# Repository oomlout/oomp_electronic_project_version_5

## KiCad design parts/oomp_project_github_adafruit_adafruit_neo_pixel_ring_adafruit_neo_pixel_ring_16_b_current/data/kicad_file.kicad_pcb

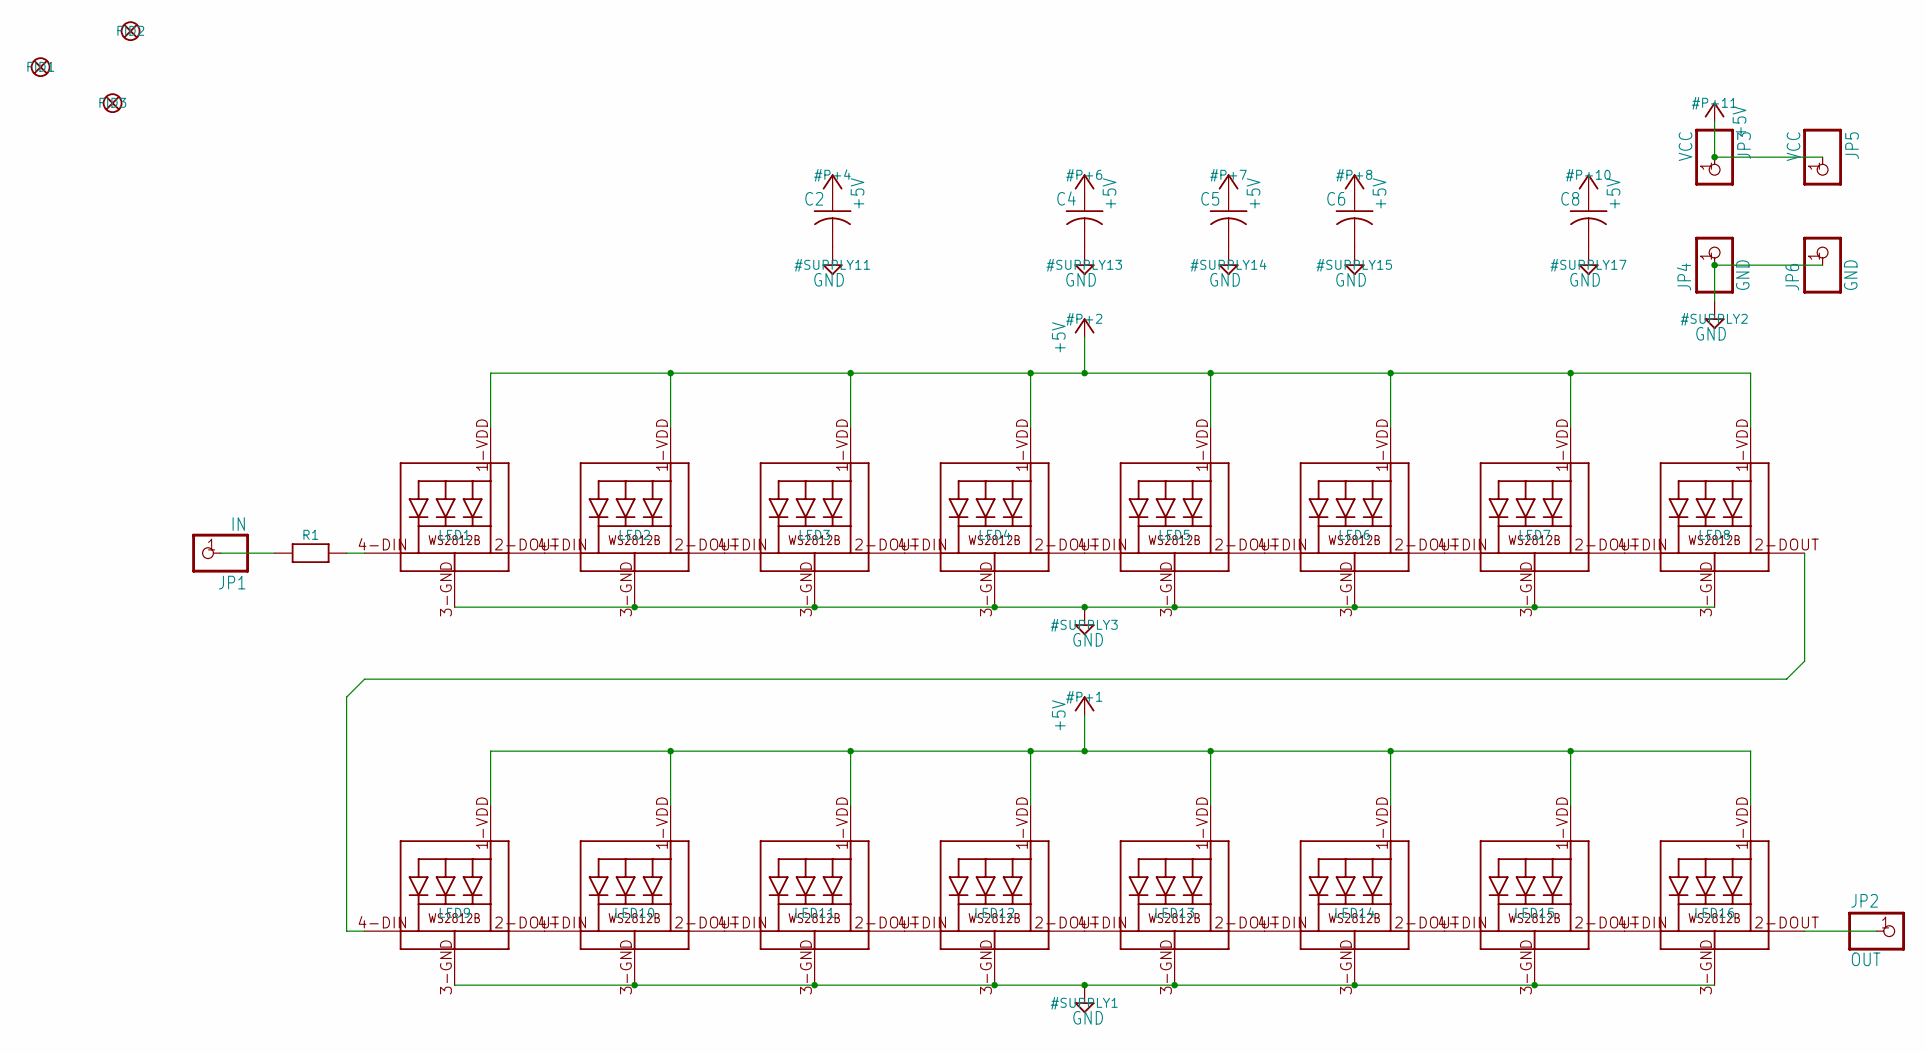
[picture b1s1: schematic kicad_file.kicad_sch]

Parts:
C2, C4, C5, C6, C8: C-USC0603K; C0603K
FID1, FID2, FID3: FIDUCIAL""; FIDUCIAL_1MM
JP1: IN; 1X01-CLEANBIG
JP2: OUT; 1X01-CLEANBIG
JP3, JP5: VCC; 1X01-CLEANBIG
JP4, JP6: GND; 1X01-CLEANBIG
LED1, LED2, LED3, LED4, LED5, LED6, LED7, LED8, LED9, LED10, LED11, LED12, LED13, LED14, LED15, LED16: WS2812B5050; WS2812B
R1: RESISTOR_0603_NOOUT; 0603-NO

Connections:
+5V: C2.1, C4.1, C5.1, C6.1, C8.1, JP3.1, JP5.1, LED1.1-VDD (VDD), LED2.1-VDD (VDD), LED3.1-VDD (VDD), LED4.1-VDD (VDD), LED5.1-VDD (VDD), LED6.1-VDD (VDD), LED7.1-VDD (VDD), LED8.1-VDD (VDD), LED9.1-VDD (VDD), LED10.1-VDD (VDD), LED11.1-VDD (VDD), LED12.1-VDD (VDD), LED13.1-VDD (VDD), LED14.1-VDD (VDD), LED15.1-VDD (VDD), LED16.1-VDD (VDD)
GND: C2.2, C4.2, C5.2, C6.2, C8.2, JP4.1, JP6.1, LED1.3-GND (GND), LED2.3-GND (GND), LED3.3-GND (GND), LED4.3-GND (GND), LED5.3-GND (GND), LED6.3-GND (GND), LED7.3-GND (GND), LED8.3-GND (GND), LED9.3-GND (GND), LED10.3-GND (GND), LED11.3-GND (GND), LED12.3-GND (GND), LED13.3-GND (GND), LED14.3-GND (GND), LED15.3-GND (GND), LED16.3-GND (GND)
IN: JP1.1, R1.1
unnamed: LED1.2-DOUT (DO), LED2.4-DIN (DI)
unnamed: LED2.2-DOUT (DO), LED3.4-DIN (DI)
unnamed: LED3.2-DOUT (DO), LED4.4-DIN (DI)
unnamed: LED4.2-DOUT (DO), LED5.4-DIN (DI)
unnamed: LED5.2-DOUT (DO), LED6.4-DIN (DI)
unnamed: LED6.2-DOUT (DO), LED7.4-DIN (DI)
unnamed: LED7.2-DOUT (DO), LED8.4-DIN (DI)
unnamed: LED1.4-DIN (DI), R1.2
unnamed: LED9.2-DOUT (DO), LED10.4-DIN (DI)
unnamed: LED10.2-DOUT (DO), LED11.4-DIN (DI)
unnamed: LED11.2-DOUT (DO), LED12.4-DIN (DI)
unnamed: LED12.2-DOUT (DO), LED13.4-DIN (DI)
unnamed: LED13.2-DOUT (DO), LED14.4-DIN (DI)
unnamed: LED14.2-DOUT (DO), LED15.4-DIN (DI)
unnamed: LED15.2-DOUT (DO), LED16.4-DIN (DI)
unnamed: LED8.2-DOUT (DO), LED9.4-DIN (DI)
OUT: JP2.1, LED16.2-DOUT (DO)

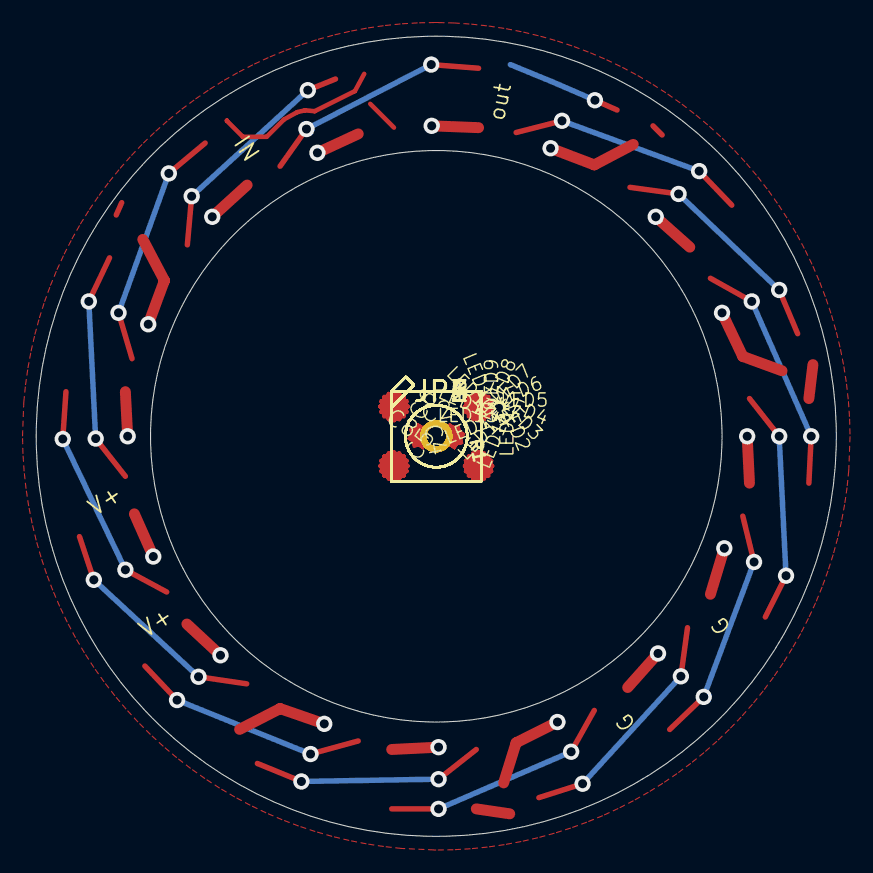
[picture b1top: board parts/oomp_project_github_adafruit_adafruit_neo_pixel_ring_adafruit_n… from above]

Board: 2 copper layers, 44.5 x 44.5 mm, 32 parts (1 on the bottom side), 20 nets.

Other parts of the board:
U$2: ADAFRUIT_5MM

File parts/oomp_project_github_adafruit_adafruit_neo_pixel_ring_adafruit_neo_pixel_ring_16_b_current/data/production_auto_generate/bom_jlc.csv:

Comment,Designator,Footprint,LCSC Part #
,R1,Adafruit NeoPixel Ring 16 B-import-fps:0603-NO,
,U$2,Adafruit NeoPixel Ring 16 B-import-fps:ADAFRUIT_5MM,
,"C2,C4,C5,C6,C8",Adafruit NeoPixel Ring 16 B-import-fps:C0603K,
GND,"JP4,JP6",Adafruit NeoPixel Ring 16 B-import-fps:1X01-CLEANBIG,C7501259
IN,JP1,Adafruit NeoPixel Ring 16 B-import-fps:1X01-CLEANBIG,C7501259
OUT,JP2,Adafruit NeoPixel Ring 16 B-import-fps:1X01-CLEANBIG,C7501259
VCC,"JP3,JP5",Adafruit NeoPixel Ring 16 B-import-fps:1X01-CLEANBIG,C7501259
WS2812B5050,"LED1,LED2,LED3,LED4,LED5,LED6,LED7,LED8,LED9,LED10,LED11,LED12,LED13,LED14,LED15,LED16",Adafruit NeoPixel Ring 16 B-import-fps:WS2812B-NARROW,

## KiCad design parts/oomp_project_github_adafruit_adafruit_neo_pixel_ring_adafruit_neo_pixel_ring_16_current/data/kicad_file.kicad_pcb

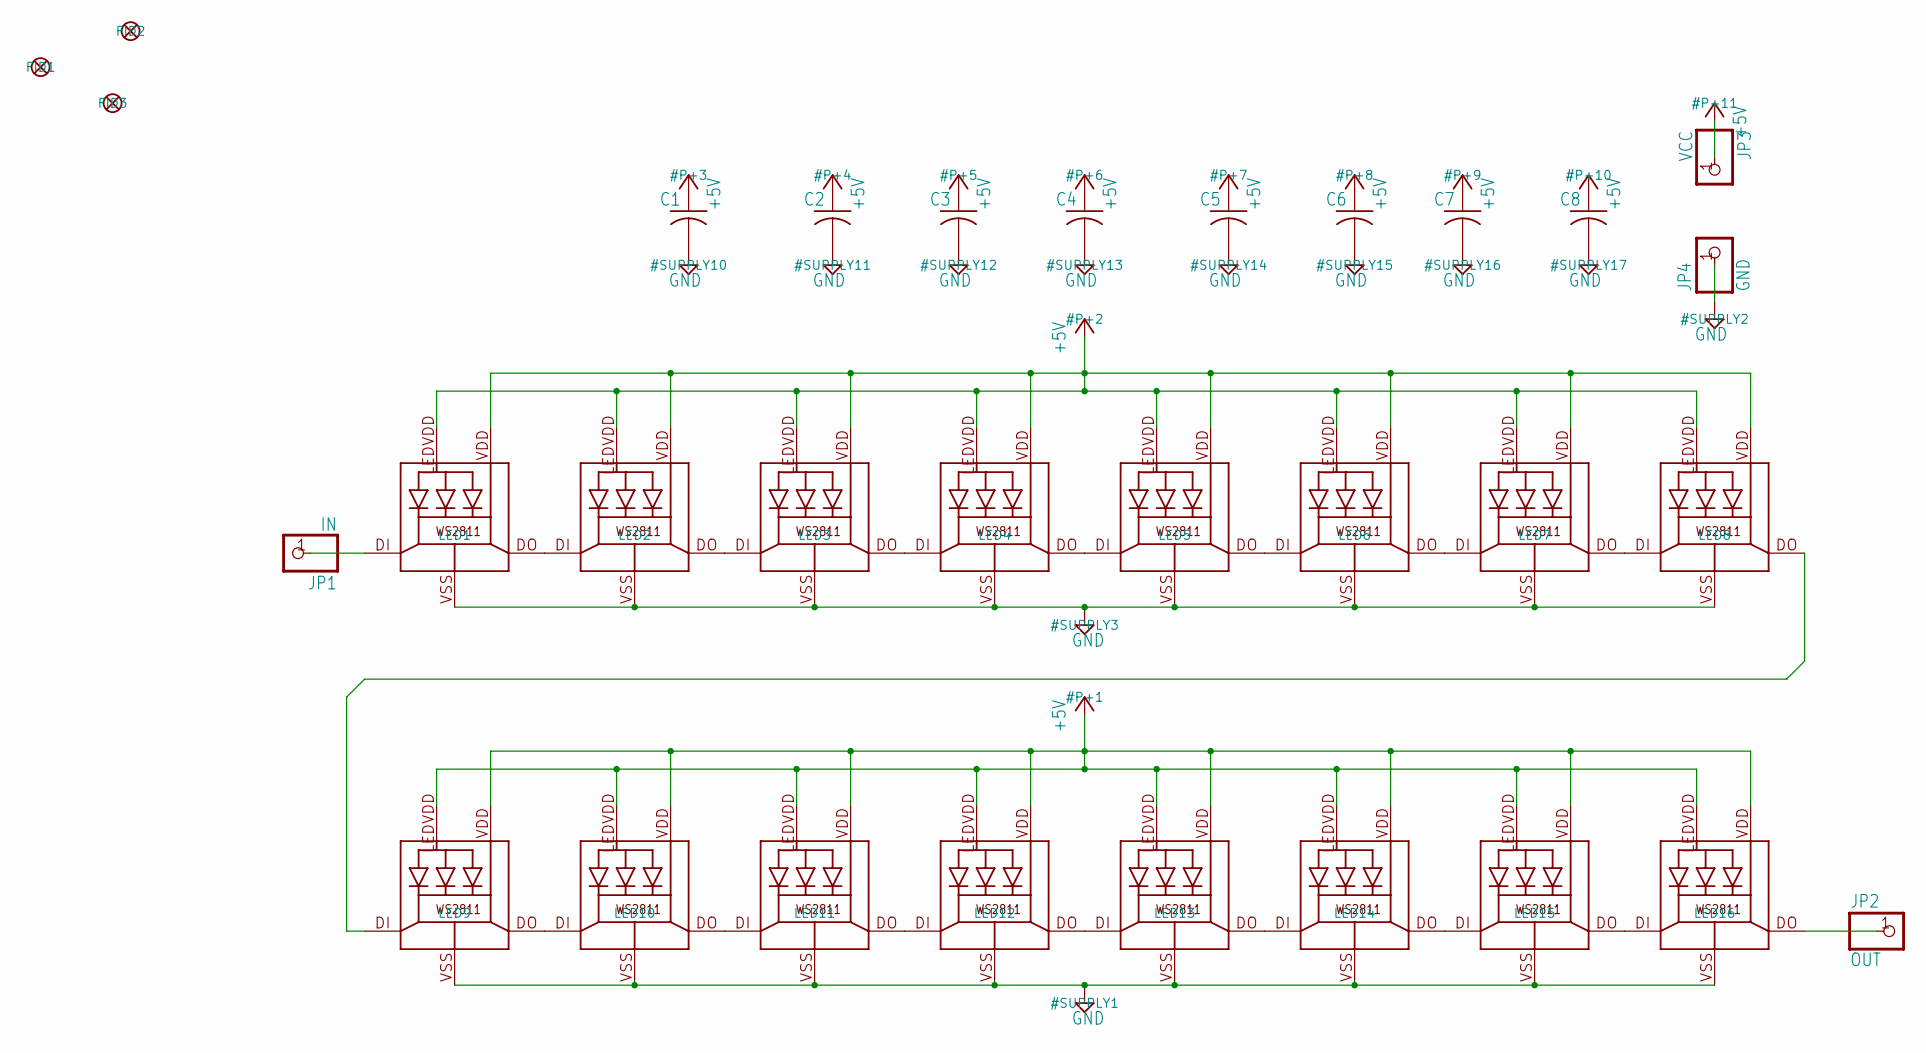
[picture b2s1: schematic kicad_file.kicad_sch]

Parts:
C1: C-USC0603; C0603
C2, C3, C4, C5, C6, C7, C8: C-USC0603K; C0603K
FID1, FID2, FID3: FIDUCIAL""; FIDUCIAL_1MM
JP1: IN; 1X01-CLEANBIG
JP2: OUT; 1X01-CLEANBIG
JP3: VCC; 1X01-CLEANBIG
JP4: GND; 1X01-CLEANBIG
LED1, LED2, LED3, LED4, LED5, LED6, LED7, LED8, LED9, LED10, LED11, LED12, LED13, LED14, LED15, LED16: WS28115050

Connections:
+5V: C1.1, C2.1, C3.1, C4.1, C5.1, C6.1, C7.1, C8.1, JP3.1, LED1.LEDVDD, LED1.VDD, LED2.LEDVDD, LED2.VDD, LED3.LEDVDD, LED3.VDD, LED4.LEDVDD, LED4.VDD, LED5.LEDVDD, LED5.VDD, LED6.LEDVDD, LED6.VDD, LED7.LEDVDD, LED7.VDD, LED8.LEDVDD, LED8.VDD, LED9.LEDVDD, LED9.VDD, LED10.LEDVDD, LED10.VDD, LED11.LEDVDD, LED11.VDD, LED12.LEDVDD, LED12.VDD, LED13.LEDVDD, LED13.VDD, LED14.LEDVDD, LED14.VDD, LED15.LEDVDD, LED15.VDD, LED16.LEDVDD, LED16.VDD
GND: C1.2, C2.2, C3.2, C4.2, C5.2, C6.2, C7.2, C8.2, JP4.1, LED1.VSS (GND), LED2.VSS (GND), LED3.VSS (GND), LED4.VSS (GND), LED5.VSS (GND), LED6.VSS (GND), LED7.VSS (GND), LED8.VSS (GND), LED9.VSS (GND), LED10.VSS (GND), LED11.VSS (GND), LED12.VSS (GND), LED13.VSS (GND), LED14.VSS (GND), LED15.VSS (GND), LED16.VSS (GND)
IN: JP1.1, LED1.DI
unnamed: LED1.DO, LED2.DI
unnamed: LED2.DO, LED3.DI
unnamed: LED3.DO, LED4.DI
unnamed: LED4.DO, LED5.DI
unnamed: LED5.DO, LED6.DI
unnamed: LED6.DO, LED7.DI
unnamed: LED7.DO, LED8.DI
unnamed: LED9.DO, LED10.DI
unnamed: LED10.DO, LED11.DI
unnamed: LED11.DO, LED12.DI
unnamed: LED12.DO, LED13.DI
unnamed: LED13.DO, LED14.DI
unnamed: LED14.DO, LED15.DI
unnamed: LED15.DO, LED16.DI
unnamed: LED8.DO, LED9.DI
OUT: JP2.1, LED16.DO

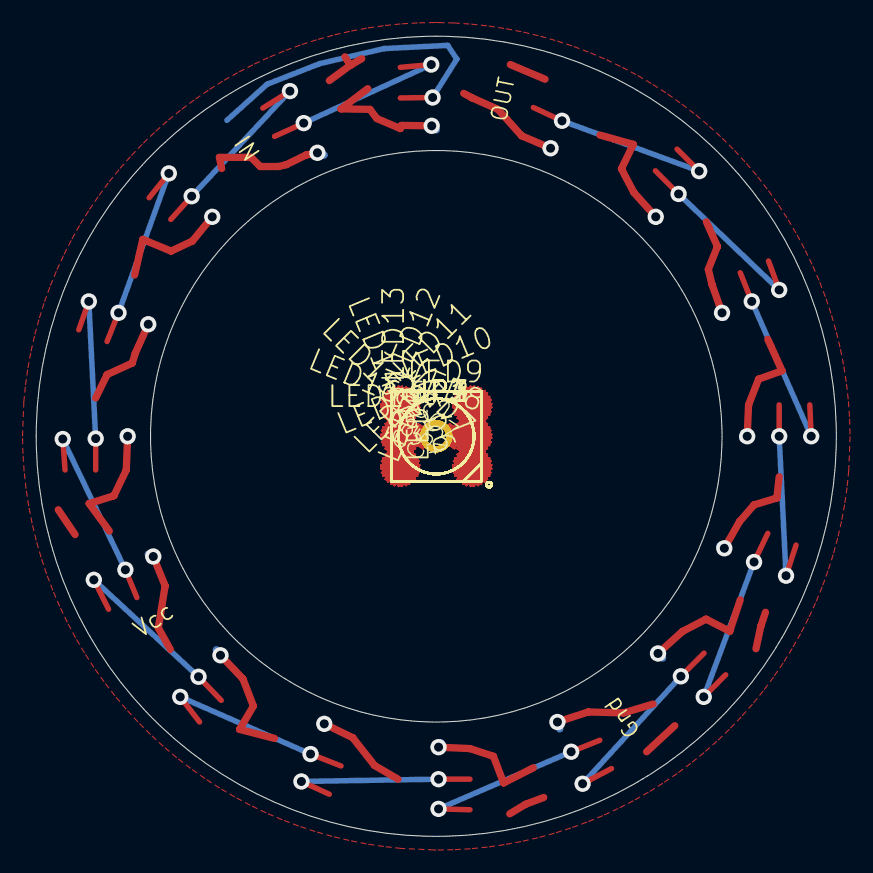
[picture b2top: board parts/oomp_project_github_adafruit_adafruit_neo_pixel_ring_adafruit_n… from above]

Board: 2 copper layers, 44.5 x 44.5 mm, 32 parts (1 on the bottom side), 19 nets.

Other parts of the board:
U$2: ADAFRUIT_5MM

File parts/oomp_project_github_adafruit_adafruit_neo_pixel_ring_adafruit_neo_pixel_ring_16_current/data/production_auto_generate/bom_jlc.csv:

Comment,Designator,Footprint,LCSC Part #
,U$2,Adafruit NeoPixel Ring 16-import-fps:ADAFRUIT_5MM,
,C1,Adafruit NeoPixel Ring 16-import-fps:C0603,
,"C2,C3,C4,C5,C6,C7,C8",Adafruit NeoPixel Ring 16-import-fps:C0603K,
GND,JP4,Adafruit NeoPixel Ring 16-import-fps:1X01-CLEANBIG,C7501259
IN,JP1,Adafruit NeoPixel Ring 16-import-fps:1X01-CLEANBIG,C7501259
OUT,JP2,Adafruit NeoPixel Ring 16-import-fps:1X01-CLEANBIG,C7501259
VCC,JP3,Adafruit NeoPixel Ring 16-import-fps:1X01-CLEANBIG,C7501259
WS28115050,"LED1,LED2,LED3,LED4,LED5,LED6,LED7,LED8,LED9,LED10,LED11,LED12,LED13,LED14,LED15,LED16",Adafruit NeoPixel Ring 16-import-fps:WS28115050,
